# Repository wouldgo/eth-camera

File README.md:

# eth-camera

An ESP32-CAM project that exposes a camera snapshot over HTTP via a wired Ethernet connection (W5500 SPI module). The device also blinks status messages in Morse code on a dedicated LED.

---

## Overview

The firmware runs on an **ESP32-CAM (AI-Thinker)** board and uses a **W5500** SPI-to-Ethernet chip to get a wired network connection. On boot it:

1. Blinks the flash LED to signal it is starting up.
2. Initialises Ethernet. DHCP runs in the background: boot does not wait for an IP address.
3. Initialises the OV2640 camera sensor.
4. Starts an HTTP server on port **3000**.
5. Every 30 s blinks the last octet of its IP address in Morse code on GPIO 33 (`0` = no IP yet).

A single HTTP endpoint is exposed:

```sh
GET http://<device-ip>:3000/snapshot
```

This returns a JPEG image taken at that moment (`image/jpeg`). While the photo is being taken the flash LED (GPIO 4) turns on, then off again. Requests are handled one at a time: a second client waits until the first one is served. A request within 3 s of the previous photo gets `429 Too Many Requests`.

---

## Hardware

The schematic is included in the `hardware/` folder (KiCad 10).

### Bill of Materials

| Ref  | Component               | Notes                                        |
|------|-------------------------|----------------------------------------------|
| U1   | ESP32-CAM (AI-Thinker)  | Main microcontroller + camera module         |
| IC1  | W5500                   | SPI Ethernet controller (via USR-ES1 module) |
| C1   | 470 µF 25 V capacitor   | Bulk decoupling on the 5 V rail              |
| C2   | 100 nF capacitor        | Bypass decoupling                            |
| J1   | 2-pin connector         | 5 V power input                              |
| SW1  | SS-12D00-G slide switch | Programming mode switch (GPIO0 to GND)       |
| SW2  | SS-12D00-G slide switch | W5500 power switch (switches its 3.3 V supply) |
| B1   | SKHLAAA010 tact button  | Reset button (to the ESP32-CAM "GND" pin next to U0T, which is RST on this board) |
| TP1  | Test point              | GND                                          |
| TP2  | Test point              | UART RX (GPIO 3)                             |
| TP3  | Test point              | UART TX (GPIO 1)                             |

### Wiring: ESP32-CAM → W5500

| ESP32-CAM GPIO | W5500 pin |
|----------------|-----------|
| GPIO 14        | SCLK      |
| GPIO 13        | MOSI      |
| GPIO 12        | MISO      |
| GPIO 2         | SCS (CS)  |
| GND            | GND       |
| 3V3 (via SW2)  | 3V3 (VCC) |

The W5500 `INT` and `RST` pins are not connected.

> **Note:** GPIO 2, 12, 13 and 14 are also the SD card lines (D0, D2, D3, CLK), so the SD card slot cannot be used together with the W5500.
>
> **Note:** the W5500 must be powered at 3.3 V (the USR-ES1 has no regulator, and the W5500 is rated for 4.6 V max). Its supply is the ESP32-CAM 3V3 pin, switched by SW2. The ESP32 pins are not 5 V tolerant.
>
> **Why the W5500 must be off while flashing:** GPIO 2 (CS) is pulled low at reset, so the W5500 is selected and drives MISO. MISO is GPIO 12, a strapping pin: if it is high at reset the ESP32 selects 1.8 V flash and the 3.3 V flash cannot be read or written.

### LEDs

| GPIO | Function                           |
|------|------------------------------------|
| 4    | Flash LED — lights during capture, dimmable via PWM (LEDC timer 1, 40 kHz) |
| 33   | Morse LED — blinks status messages |

### Programming

To flash the firmware:

1. Set **SW1** to connect GPIO 0 to GND.
2. Power off the W5500 with **SW2** (see the strapping note above).
3. Connect a USB-UART adapter to TP3 (GPIO 1, TX), TP2 (GPIO 3, RX) and TP1 (GND).
4. Press the reset button (B1), then flash with `idf.py flash`.
5. After flashing, set SW1 back to normal, power the W5500 on with SW2, and reset.

---

## Software

### Prerequisites

- [ESP-IDF](https://docs.espressif.com/projects/esp-idf/en/stable/esp32/get-started/) v5.x
- CMake ≥ 3.16

### Build & Flash

```bash
# Set up ESP-IDF environment (run once per shell session)
. $IDF_PATH/export.sh

# Build
idf.py build

# Flash and monitor
idf.py -p /dev/ttyUSB0 flash monitor
```

### Configuration

`sdkconfig.defaults` sets sensible defaults for the ESP32-CAM:

| Setting                  | Value           |
|--------------------------|-----------------|
| CPU frequency            | 240 MHz         |
| Flash size               | 4 MB            |
| Flash frequency          | 80 MHz          |
| Flash mode               | QIO             |
| PSRAM                    | Enabled, 80 MHz |
| FreeRTOS tick rate       | 1000 Hz         |

The W5500 Ethernet driver must be enabled. It is configured via `CONFIG_ETH_SPI_ETHERNET_W5500=y` (set in `sdkconfig.defaults`). The ESP32 internal Ethernet MAC is disabled (`CONFIG_ETH_USE_ESP32_EMAC=n`).

### Dependencies

Managed via [ESP-IDF Component Manager](https://docs.espressif.com/projects/idf-component-manager/en/latest/):

| Component                  | Version |
|----------------------------|---------|
| `espressif/esp32-camera`   | ^2.1.4  |

Dependencies are resolved automatically during build.

---

## Project Structure

```sh
eth-camera/
├── main/
│   ├── app_main.c        # Entry point, boot sequence
│   ├── camera.c / .h     # Camera init and frame capture (OV2640)
│   ├── http.c / .h       # HTTP server, /snapshot endpoint
│   ├── leds.c / .h       # Flash LED + Morse LED with queue
│   └── net/
│       ├── net.c / .h    # Ethernet init (W5500 over SPI)
├── hardware/
│   ├── eth-camera.kicad_sch   # Schematic
│   ├── eth-camera.kicad_pro   # KiCad project file
│   ├── board.scad             # Board reference model (not printed)
│   ├── chassis.scad           # Chassis: tray + lid
│   ├── meter_mount.scad       # Cone mount to the water meter
│   └── tray.stl / lid.stl / meter_mount.stl   # Printable parts
├── CMakeLists.txt
├── sdkconfig.defaults
└── README.md
```

---

## Device Hostname

On boot the firmware derives a unique hostname from the ESP32 factory MAC address:

```sh
camera-XXYYZZ
```

where `XXYYZZ` are the last three bytes of the MAC. The hostname is set on the DHCP/netif layer so it may appear in your router's DHCP table.

---

## API

### `GET /snapshot`

Takes a photo (1600×1200 UXGA) and sends it back as JPEG. The flash turns on and a couple of frames are discarded so exposure adapts before the real shot.

**Query parameters:**

| Name    | Values   | Default | Meaning                                  |
|---------|----------|---------|------------------------------------------|
| `flash` | `0`–`100`| `10`    | Flash brightness in % (PWM duty, `0` = off) |

```sh
curl -o photo.jpg "http://<device-ip>:3000/snapshot?flash=25"
```

**Response headers:**

| Header          | Value            |
|-----------------|------------------|
| Content-Type    | `image/jpeg`     |
| Content-Length  | image size       |
| Cache-Control   | `no-store`       |
| Connection      | `close`          |

**Error responses:**

| Status | Meaning                                  |
|--------|------------------------------------------|
| 400    | `flash` is not an integer in `0`–`100`   |
| 429    | Less than 3 s since the previous photo (`Retry-After: 3`) |
| 503    | Capture failed                           |

> **Security:** the endpoint has no authentication. Expose it only on a trusted LAN.

---

## License

See `managed_components/espressif__esp32-camera/LICENSE` for the camera component license.

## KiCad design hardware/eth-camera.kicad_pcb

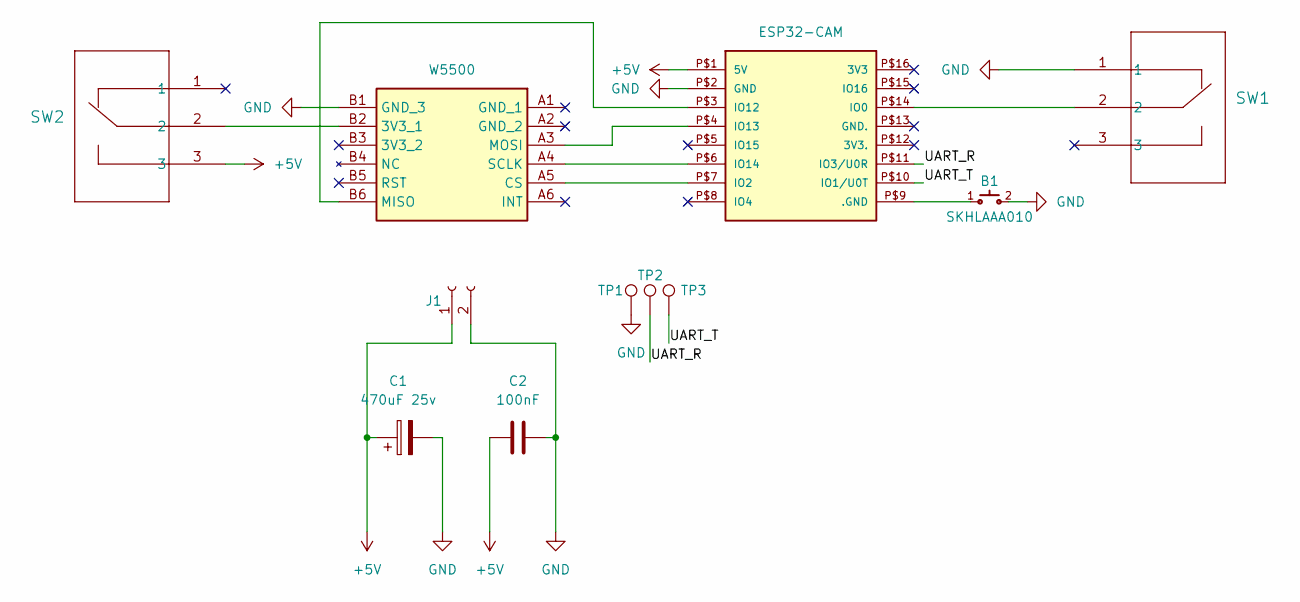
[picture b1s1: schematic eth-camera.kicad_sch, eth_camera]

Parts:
B1: SKHLAAA010
C1: 470uF 25v; CP_Radial_D10.0mm_P5.00mm
C2: 100nF; C_Disc_D4.7mm_W2.5mm_P5.00mm
IC1: W5500; USRES1_W_HEADERS; Manufacturer_Part_Number USR-ES1
J1: Conn_01x02_Socket; PinSocket_1x02_P2.54mm_Vertical
SW1, SW2: SS-12D00-G 4 E; 1P2T_SS-12D00_CNK
TP1, TP2, TP3: TestPoint; PinSocket_1x01_P2.54mm_Vertical
U1: ESP32-CAM; ESP32-CAM_W_HEADERS

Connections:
+5V: C1.1, C2.1, J1.1, SW2.3, U1.P$1 (5V)
/UART_R: TP2.1 (1_1), U1.P$11 (IO3/U0R)
/UART_T: TP3.1 (1_1), U1.P$10 (IO1/U0T)
GND: B1.2, C1.2, C2.2, IC1.B1 (GND_3), J1.2, SW1.1, TP1.1 (1_1), U1.P$2 (GND)
unnamed: IC1.B2 (3V3_1), SW2.2
unnamed: IC1.A5 (CS), U1.P$7 (IO2)
unnamed: IC1.B6 (MISO), U1.P$3 (IO12)
unnamed: IC1.A3 (MOSI), U1.P$4 (IO13)
unnamed: IC1.A4 (SCLK), U1.P$6 (IO14)
unnamed: B1.1, U1.P$9 (.GND)
unnamed: SW1.2, U1.P$14 (IO0)

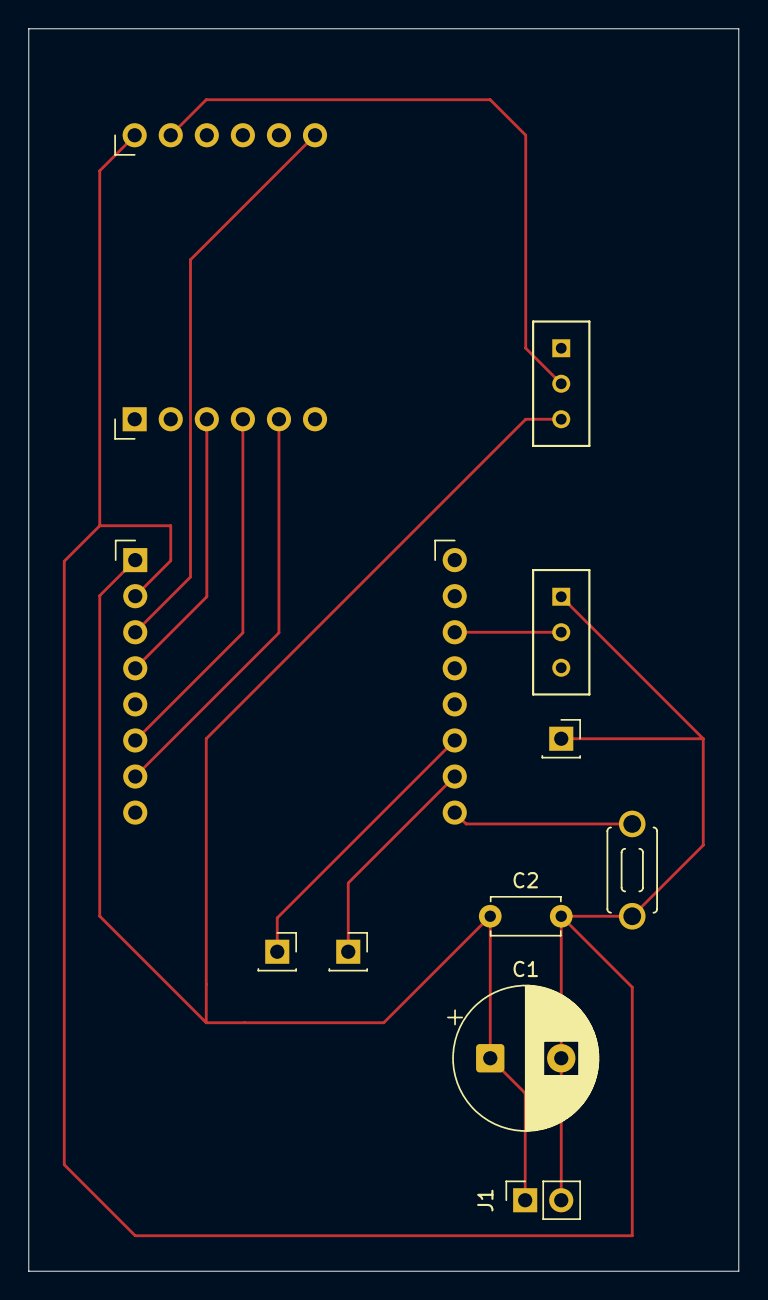
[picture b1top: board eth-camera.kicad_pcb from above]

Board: 2 copper layers, 50.0 x 87.5 mm, 11 parts (0 on the bottom side), 11 nets.

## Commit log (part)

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2026-06-14 feature(camera): http camera + ligth before taking photo, wired to eth
